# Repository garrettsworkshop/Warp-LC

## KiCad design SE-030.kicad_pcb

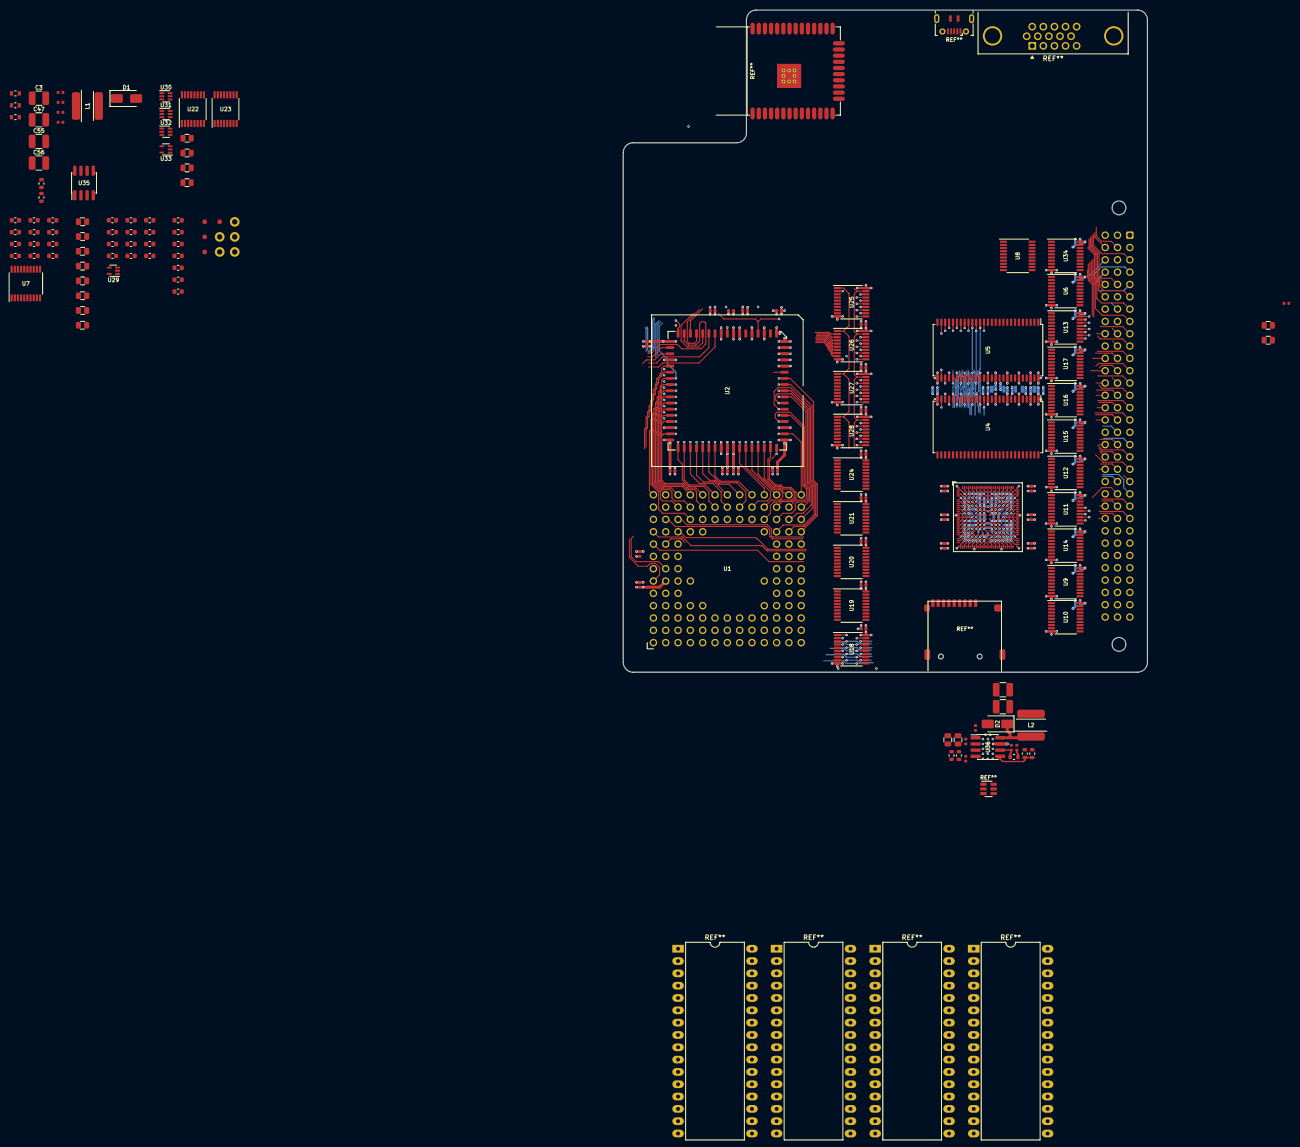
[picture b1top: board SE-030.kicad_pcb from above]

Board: 6 copper layers, 108.1 x 136.5 mm, 121 parts (1 on the bottom side), 229 nets.

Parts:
C1, C2, C54, C61: 100n; C_0402
C3, C47, C55, C56: 47u; C_1210
C4, C5, C6, C7, C8, C9, C10, C11, C12, C13, C14, C15, C57, C58, C59, C60: 10u; C_0805
C16, C17, C18, C19, C20, C21, C22, C23, C24, C25, C26, C27, C28, C29, C30, C31, C32, C33, C34, C35, C36, C37, C38, C39, C40, C41, C42, C43, C44, C45, C46: 2u2; C_0603
C48, C53: 10n; C_0402
C49, C52: 1n; C_0402
C50, C51: 47p; C_0402
D1, D2: B340LB; D_SMA
FID1, FID2, FID3, FID4: Fiducial
H1, H2, H3, H4, H5: PasteHole_1.1mm_PTH
J2: MacLCPDS; DIN41612_R_3x32_Male_Vertical_THT
L1, L2: 4u7; TaiyoYuden_NRS6028
R5, R13: 3k3; R_0603
R6: 10k; R_0603
R7, R10: 29k4; R_0603
R8, R9, R11, R12: Rl; R_0603
R14: 8k2; R_0603
U1: MC68030RC; PGA-128_MC68030
U2: MC68882FN; PLCC-68_SMDSocket
U3: LFE5U-12F-BG256; Lattice_CABGA-256_14x14mm
U4, U5: W9825G6KH-6; TSOP-II-54_22.2x10.16mm_P0.8mm
U6, U8, U9, U10, U11, U12, U34: 74AHCT573PW; TSSOP-20_4.4x6.5mm_P0.65mm
U7, U18, U19, U20, U21, U24: 74LVC244APW; TSSOP-20_4.4x6.5mm_P0.65mm
U13: 74LVC245APW; TSSOP-20_4.4x6.5mm_P0.65mm
U14, U15, U16, U17, U25, U26, U27, U28: 74AHC245APW; TSSOP-20_4.4x6.5mm_P0.65mm
U22, U23: 74LVC138APW; TSSOP-16_4.4x5mm_P0.65mm
U29: 74LVC1G125GW; SOT-353
U30: 741G3208GW; SOT-363
U31, U32: 74LVC1G332GW; SOT-363
U33: 741G08GW; SOT-353
U35, U36: TPS54331D; SOIC-8_3.9mm

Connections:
+1V1: C55.1, C56.1, L2.2, R13.1, U3.G6 (Vcc), U3.G7 (Vcc), U3.G9 (Vcc), U3.L8 (Vcc), U3.L9 (Vcc), U3.L10 (Vcc)
+2V5: U3.G11 (VccAUX), U3.L7 (VccAUX)
+3V3: C3.1, C16.1, C17.1, C18.1, C19.1, C20.1, C21.1, C22.1, C23.1, C24.1, C25.1, C26.1, C27.1, C28.1, C29.1, C30.1, C31.1, C32.1, C33.1, C34.1, C35.1, C36.1, C37.1, C38.1, C39.1, C40.1, C41.1, C42.1, C43.1, C44.1, C45.1, C46.1, C47.1, L1.2, R6.1, U3.F6 (VccIO0), U3.F7 (VccIO0), U3.F10 (VccIO1), U3.F11 (VccIO1), U3.H6 (VccIO7), U3.H7 (VccIO7), U3.H11 (VccIO2), U3.J6 (VccIO6), U3.J7 (VccIO6), U3.J11 (VccIO2), U3.K11 (VccIO3), U3.L6 (VccIO8), U3.L11 (VccIO3), U4.1, U4.3, U4.9, U4.14, U4.27, U4.43, U4.49, U5.1, U5.3, U5.9, U5.14, U5.27, U5.43, U5.49, U7.20 (Vcc), U13.20 (Vcc), U14.20 (Vcc), U15.20 (Vcc), U16.20 (Vcc), U17.20 (Vcc), U18.20 (Vcc), U19.20 (Vcc), U20.20 (Vcc), U21.20 (Vcc), U22.16 (Vcc), U23.16 (Vcc), U24.20 (Vcc), U25.20, U26.20, U27.20, U28.20, U29.5 (Vcc), U30.5 (Vcc), U31.5 (Vcc), U32.5 (Vcc), U33.5 (Vcc)
+5V: C4.1, C5.1, C12.1, C13.1, C14.1, C15.1, J2.B3 (+5V), J2.B4 (+5V), U1.A1 (~BR), U1.C3 (~BGACK), U1.C6 (Vcc), U1.D4 (Vcc), U1.D10 (Vcc), U1.F2 (Vcc), U1.F11 (Vcc), U1.F13 (~MMUDIS), U1.H1 (Vcc), U1.H3 (Vcc), U1.H12 (~CDIS), U1.K4 (Vcc), U1.K10 (Vcc), U1.L6 (Vcc), U2.10, U2.16, U2.17, U2.18, U2.26, U2.27, U2.43, U2.52, U2.53, U2.61, U6.11 (~LE), U6.20 (Vcc), U8.20 (Vcc), U9.20 (Vcc), U10.20 (Vcc), U11.20 (Vcc), U12.20 (Vcc), U34.11 (~LE), U34.20 (Vcc)
+12V: C8.1, C9.1, J2.A32 (+12V)
-5V: C6.1, C7.1, J2.C32 (-5V)
-12V: C10.1, C11.1
/CPUBuf/A13: U1.A12 (A13), U23.6 (E3)
/CPUBuf/A14: U1.B10 (A14), U23.3 (A2)
/CPUBuf/A15: U1.A11 (A15), U23.2 (A1)
/CPUBuf/A16: U1.B9 (A16), U23.1 (A0)
/CPUBuf/A17: U1.A10 (A17), U22.6 (E3)
/CPUBuf/A18: U1.C8 (A18), U23.5 (~E2)
/CPUBuf/A19: U1.A9 (A19), U22.5 (~E2)
/CPUBuf/A30: U1.A3 (A30), U31.3 (B)
/CPUBuf/A31: U1.B3 (A31), U31.1 (A)
/CPUBuf/CPU_D0: U2.3, U25.9
/CPUBuf/CPU_D1: U2.2, U25.8
/CPUBuf/CPU_D2: U2.1, U25.6
/CPUBuf/CPU_D3: U2.68, U25.4
/CPUBuf/CPU_D4: U2.67, U25.2
/CPUBuf/CPU_D5: U2.66, U25.3
/CPUBuf/CPU_D6: U2.65, U25.5
/CPUBuf/CPU_D7: U2.64, U25.7
/CPUBuf/CPU_D8: U2.62, U26.3
/CPUBuf/CPU_D9: U2.60, U26.2
/CPUBuf/CPU_D10: U2.59, U26.4
/CPUBuf/CPU_D11: U2.58, U26.5
/CPUBuf/CPU_D12: U2.57, U26.6
/CPUBuf/CPU_D13: U2.56, U26.7
/CPUBuf/CPU_D14: U2.55, U26.8
/CPUBuf/CPU_D15: U2.54, U26.9
/CPUBuf/CPU_D16: U2.50, U27.2
/CPUBuf/CPU_D17: U2.49, U27.3
/CPUBuf/CPU_D18: U2.48, U27.4
/CPUBuf/CPU_D19: U2.47, U27.5
/CPUBuf/CPU_D20: U2.46, U27.6
/CPUBuf/CPU_D21: U2.45, U27.7
/CPUBuf/CPU_D22: U2.44, U27.9
/CPUBuf/CPU_D23: U2.42, U27.8
/CPUBuf/CPU_D24: U2.40, U28.2
/CPUBuf/CPU_D25: U2.39, U28.3
/CPUBuf/CPU_D26: U2.38, U28.4
/CPUBuf/CPU_D27: U2.37, U28.5
/CPUBuf/CPU_D28: U2.36, U28.6
/CPUBuf/CPU_D29: U2.35, U28.7
/CPUBuf/CPU_D30: U2.34, U28.8
/CPUBuf/CPU_D31: U2.33, U28.9
/CPUBuf/FC0: U1.D2 (FC0), U22.1 (A0), U24.15 (2A1)
/CPUBuf/FC1: U1.C1 (FC1), U22.2 (A1), U24.17 (2A0)
/CPUBuf/FC2: U1.D1 (FC2), U22.3 (A2), U24.8 (1A3)
/CPUBuf/R~W: U1.L3 (R~W), U24.4 (1A1), U24.6 (1A2), U31.6 (C)
/CPUBuf/SIZ0: U1.L2 (SIZ0), U24.13 (2A2)
/CPUBuf/SIZ1: U1.K3 (SIZ1), U24.11 (2A3)
/CPUBuf/~AS: U1.J2 (~AS), U7.17 (2A0), U33.1 (A)
/CPUBuf/~CBREQ: U1.K1 (~CBREQ), U7.13 (2A2)
/Control/CCLK: U1.E1 (CLK), U3.N9 (CCLK), U33.2 (B)
/Control/CPU_DDIR: U25.1, U26.1, U27.1, U28.1
/Control/CPU_D~OE: U25.19, U26.19, U27.19, U28.19
/Control/IOA~OE: U6.1 (~OE), U9.1 (~OE), U10.1 (~OE), U11.1 (~OE), U12.1 (~OE), U34.1 (~OE)
/Control/IOD~OE: U14.19 (~OE), U15.19 (~OE), U16.19 (~OE), U17.19 (~OE)
/Control/RAM_~CAS: U4.17, U5.17
/Control/RAM_~CS: U4.19, U5.19
/Control/RAM_~RAS: U4.18, U5.18
/Control/RAM_~WE: U4.16, U5.16
/MC68k/~IPL0: J2.A22 (~IPL0), U1.H13 (~IPL0)
/MC68k/~IPL1: J2.C21 (~IPL1), U1.G13 (~IPL1)
/MC68k/~IPL2: J2.B21 (~IPL2), U1.G12 (~IPL2)
/MC68k/~RESET: J2.C7 (~RESET), U1.F12 (~RESET), U13.12 (B6)
/MC68k/~STERM: U1.G1 (~STERM), U30.4 (Y)
/PDS/A0: J2.C17 (A0), U6.17 (Q2), U12.19 (Q0)
/PDS/A1: J2.A18 (A1), U6.16 (Q3), U12.18 (Q1)
/PDS/A2: J2.B25 (A2), U9.18 (Q1)
/PDS/A3: J2.C25 (A3), U9.17 (Q2)
/PDS/A4: J2.A25 (A4), U9.19 (Q0)
/PDS/A5: J2.C26 (A5), U9.14 (Q5)
/PDS/A6: J2.A26 (A6), U9.16 (Q3)
/PDS/A7: J2.C27 (A7), U10.19 (Q0)
/PDS/A8: J2.B28 (A8), U10.17 (Q2)
/PDS/A9: J2.A28 (A9), U10.18 (Q1)
/PDS/A10: J2.C28 (A10), U10.16 (Q3)
/PDS/A11: J2.A27 (A11), U9.13 (Q6)
/PDS/A12: J2.B26 (A12), U9.15 (Q4)
/PDS/A13: J2.B27 (A13), U9.12 (Q7)
/PDS/A14: J2.C29 (A14), U10.13 (Q6)
/PDS/A15: J2.B29 (A15), U10.14 (Q5), U11.12 (Q7)
/PDS/A16: J2.A29 (A16), U10.15 (Q4), U11.13 (Q6)
/PDS/A17: J2.B30 (A17), U11.14 (Q5)
/PDS/A18: J2.A30 (A18), U10.12 (Q7), U11.15 (Q4)
/PDS/A19: J2.C30 (A19), U11.16 (Q3)
/PDS/A20: J2.A21 (A20), U11.17 (Q2)
/PDS/A21: J2.C20 (A21), U11.18 (Q1)
/PDS/A22: J2.B20 (A22), U11.19 (Q0)
/PDS/A23: J2.A20 (A23), U12.12 (Q7)
/PDS/A24: J2.C19 (A24), U12.13 (Q6)
/PDS/A25: J2.B19 (A25), U12.14 (Q5)
/PDS/A26: J2.A19 (A26), U12.15 (Q4)
/PDS/A27: J2.C18 (A27), U12.16 (Q3)
/PDS/A31: J2.B18 (A31), U12.17 (Q2)
/PDS/C16M: J2.B7 (C16M), U13.14 (B4)
/PDS/D0: J2.B24 (D0), U14.12 (B6)
/PDS/D1: J2.A24 (D1), U14.13 (B5)
/PDS/D2: J2.A23 (D2), U14.16 (B2)
/PDS/D3: J2.B22 (D3), U14.18 (B0)
/PDS/D4: J2.C22 (D4), U14.17 (B1)
/PDS/D5: J2.B23 (D5), U14.15 (B3)
/PDS/D6: J2.C23 (D6), U14.14 (B4)
/PDS/D7: J2.C24 (D7), U14.11 (B7)
/PDS/D8: J2.C16 (D8), U15.11 (B7)
/PDS/D9: J2.B16 (D9), U15.12 (B6)
/PDS/D10: J2.A16 (D10), U15.13 (B5)
/PDS/D11: J2.C15 (D11), U15.14 (B4)
/PDS/D12: J2.B15 (D12), U15.15 (B3)
/PDS/D13: J2.A15 (D13), U15.16 (B2)
/PDS/D14: J2.C14 (D14), U15.17 (B1)
/PDS/D15: J2.B14 (D15), U15.18 (B0)
/PDS/D16: J2.A14 (D16), U16.11 (B7)
/PDS/D17: J2.C13 (D17), U16.12 (B6)
/PDS/D18: J2.B13 (D18), U16.13 (B5)
/PDS/D19: J2.A13 (D19), U16.14 (B4)
/PDS/D20: J2.C12 (D20), U16.15 (B3)
/PDS/D21: J2.B12 (D21), U16.16 (B2)
/PDS/D22: J2.A12 (D22), U16.17 (B1)
/PDS/D23: J2.C11 (D23), U16.18 (B0)
/PDS/D24: J2.B11 (D24), U17.11 (B7)
/PDS/D25: J2.A11 (D25), U17.12 (B6)
/PDS/D26: J2.C10 (D26), U17.13 (B5)
/PDS/D27: J2.B10 (D27), U17.14 (B4)
/PDS/D28: J2.A10 (D28), U17.15 (B3)
/PDS/D29: J2.C9 (D29), U17.16 (B2)
/PDS/D30: J2.B9 (D30), U17.17 (B1)
/PDS/D31: J2.A9 (D31), U17.18 (B0)
/PDS/FC0: J2.A7 (FC0), U6.19 (Q0)
/PDS/FC1: J2.C6 (FC1), U34.12 (Q7)
/PDS/FC2: J2.A6 (FC2), U34.13 (Q6)
/PDS/R~W: J2.B2 (R~W), U34.19 (Q0)
/PDS/SIZ0: J2.C5 (SIZ0), U34.14 (Q5)
/PDS/SIZ1: J2.B5 (SIZ1), U34.15 (Q4)
/PDS/~AS: J2.A3 (~AS), U34.16 (Q3)
/PDS/~BERR: J2.C3 (~BERR), U13.19 (~OE)
/PDS/~BR: J2.B17 (~BR), U8.14 (Q5)
/PDS/~DSACK0: J2.C4 (~DSACK0), U13.17 (B1)
/PDS/~DSACK1: J2.A4 (~DSACK1), U13.18 (B0)
/PDS/~DS: J2.C2 (~DS), U34.17 (Q2)
/PDS/~HALT: J2.A5 (~HALT), U13.16 (B2)
/PDS/~RMC: J2.A8 (~RMC), U6.18 (Q1)
/PDSBuf/AD0: U8.9 (D7), U12.2 (D0)
/PDSBuf/AD1: U8.8 (D6), U12.3 (D1)
/PDSBuf/AD3: U8.6 (D4), U12.5 (D3)
/PDSBuf/AD4: U8.5 (D3), U12.6 (D4)
/PDSBuf/AD5: U8.4 (D2), U12.7 (D5)
/PDSBuf/AD6: U8.3 (D1), U12.8 (D6)
/PDSBuf/AD7: U8.2 (D0), U12.9 (D7)
/PDSBuf/AoutLE: U9.11 (~LE), U10.11 (~LE), U11.11 (~LE), U12.11 (~LE)
/PDSBuf/DDIR: U14.1 (AtoB), U15.1 (AtoB), U16.1 (AtoB), U17.1 (AtoB), U34.18 (Q1)
/PDSBuf/FSB_A25: U9.5 (D3), U9.8 (D6)
/PDSBuf/FSB_A26: U9.4 (D2), U9.7 (D5)
/PDSBuf/FSB_A27: U9.2 (D0), U9.3 (D1), U9.6 (D4)
/PDSBuf/IOR~W: U34.2 (D0), U34.3 (D1)
/PDSBuf/LFC0: U6.2 (D0), U8.16 (Q3)
/PDSBuf/LFC1: U8.17 (Q2), U34.9 (D7)
/PDSBuf/LFC2: U8.18 (Q1), U34.8 (D6)
/RAM/BA0: U4.20, U5.20
/RAM/BA1: U4.21, U5.21
/RAM/CKE: U4.37, U5.37
/RAM/D0: U4.2, U25.11
/RAM/D1: U4.4, U25.12
/RAM/D2: U4.5, U25.14
/RAM/D3: U4.7, U25.16
/RAM/D4: U4.8, U25.18
/RAM/D5: U4.10, U25.17
/RAM/D6: U4.11, U25.15
/RAM/D7: U4.13, U25.13
/RAM/D8: U4.42, U26.17
/RAM/D9: U4.44, U26.18
/RAM/D10: U4.45, U26.16
/RAM/D11: U4.47, U26.15
/RAM/D12: U4.48, U26.14
/RAM/D13: U4.50, U26.13
/RAM/D14: U4.51, U26.12
/RAM/D15: U4.53, U26.11
/RAM/D16: U5.2, U27.18
/RAM/D17: U5.4, U27.17
/RAM/D18: U5.5, U27.16
/RAM/D19: U5.7, U27.15
/RAM/D20: U5.8, U27.14
/RAM/D21: U5.10, U27.13
/RAM/D22: U5.11, U27.11
/RAM/D23: U5.13, U27.12
/RAM/D24: U5.42, U28.18
/RAM/D25: U5.44, U28.17
/RAM/D26: U5.45, U28.16
/RAM/D27: U5.47, U28.15
/RAM/D28: U5.48, U28.14
/RAM/D29: U5.50, U28.13
/RAM/D30: U5.51, U28.12
/RAM/D31: U5.53, U28.11
/RAM/RA0: U4.23, U5.23
/RAM/RA1: U4.24, U5.24
/RAM/RA2: U4.25, U5.25
/RAM/RA3: U4.26, U5.26
/RAM/RA4: U4.29, U5.29
/RAM/RA5: U4.30, U5.30
/RAM/RA6: U4.31, U5.31
/RAM/RA7: U4.32, U5.32
/RAM/RA8: U4.33, U5.33
/RAM/RA9: U4.34, U5.34
/RAM/RA10: U4.22, U5.22
/RAM/RA11: U4.35, U5.35
/RAM/RA12: U4.36, U5.36
GND: C1.2, C3.2, C4.2, C5.2, C6.2, C7.2, C8.2, C9.2, C10.2, C11.2, C12.2, C13.2, C14.2, C15.2, C16.2, C17.2, C18.2, C19.2, C20.2, C21.2, C22.2, C23.2, C24.2, C25.2, C26.2, C27.2, C28.2, C29.2, C30.2, C31.2, C32.2, C33.2, C34.2, C35.2, C36.2, C37.2, C38.2, C39.2, C40.2, C41.2, C42.2, C43.2, C44.2, C45.2, C46.2, C47.2, C48.2, C49.2, C50.2, C51.2, C52.2, C53.2, C55.2, C56.2, C57.2, C58.2, C59.2, C60.2, C61.2, D1.2 (A), D2.2 (A), H1.1, H2.1, H3.1, H4.1, H5.1, J2.B6 (GND), J2.B8 (GND), J2.B32 (GND), R5.2, R9.2, R12.2, R14.2, U1.C5 (GND), U1.C7 (GND), U1.C9 (GND), U1.E2 (~AVEC), U1.E3 (GND), U1.E11 (GND), U1.F3 (GND), U1.G3 (GND), U1.G11 (GND), U1.J3 (GND), U1.J11 (GND), U1.L5 (GND), U1.L7 (GND), U1.L8 (GND), U1.L9 (GND), U2.5, U2.6, U2.7, U2.8, U2.9, U2.12, U2.14, U2.19, U2.30, U2.41, U2.51, U2.63, U3.A1 (GND), U3.A16 (GND), U3.D2 (GND), U3.D15 (GND), U3.F8 (GND), U3.F9 (GND), U3.G8 (GND), U3.G10 (GND), U3.H1 (GND), U3.H8 (GND), U3.H9 (GND), U3.H10 (GND), U3.H16 (GND), U3.J8 (GND), U3.J9 (GND), U3.J10 (GND), U3.K6 (GND), U3.K7 (GND), U3.K8 (GND), U3.K9 (GND), U3.K10 (GND), U3.N2 (GND), U3.N15 (GND), U3.T1 (GND), U3.T5 (GND), U3.T12 (GND), U3.T16 (GND), U4.6, U4.12, U4.28, U4.41, U4.46, U4.52, U4.54, U5.6, U5.12, U5.28, U5.41, U5.46, U5.52, U5.54, U6.10 (GND), U7.1 (1~OE), U7.2 (1A0), U7.4 (1A1), U7.5 (2Y1), U7.6 (1A2), U7.8 (1A3), U7.9 (2Y3), U7.10 (GND), U7.11 (2A3), U7.12 (1Y3), U7.14 (1Y2), U7.15 (2A1), U7.16 (1Y1), U7.18 (1Y0), U7.19 (2~OE), U8.1 (~OE), U8.10 (GND), U9.10 (GND), U10.10 (GND), U11.10 (GND), U12.10 (GND), U13.1 (AtoB), U13.6 (A4), U13.8 (A6), U13.10 (GND), U13.11 (B7), U13.13 (B5), U13.15 (B3), U14.10 (GND), U15.10 (GND), U16.10 (GND), U17.10 (GND), U18.1 (1~OE), U18.10 (GND), U18.19 (2~OE), U19.1 (1~OE), U19.10 (GND), U19.19 (2~OE), U20.1 (1~OE), U20.10 (GND), U20.19 (2~OE), U21.1 (1~OE), U21.10 (GND), U21.19 (2~OE), U22.4 (~E1), U22.8 (GND), U23.4 (~E1), U23.8 (GND), U24.1 (1~OE), U24.10 (GND), U24.19 (2~OE), U25.10, U26.10, U27.10, U28.10, U29.2 (A), U29.3 (GND), U30.2 (GND), U31.2 (GND), U32.2 (GND), U33.3 (GND), U34.10 (GND), U35.7 (GND), U36.7 (GND)
unnamed: C49.1, R7.2
unnamed: C52.1, R10.2
unnamed: C2.2, D1.1 (K), L1.1, U35.8 (PH)
unnamed: C54.2, D2.1 (K), L2.1, U36.8 (PH)
unnamed: U22.7 (~Q7), U32.1 (A)
unnamed: U23.15 (~Q0), U32.3 (B)
unnamed: U30.1 (A), U31.4 (Y)
unnamed: C2.1, U35.1 (BOOT)
unnamed: C50.1, R7.1, U35.6 (COMP)
unnamed: R8.2, R9.1, U35.3 (EN)
unnamed: C48.1, U35.4 (SS)
unnamed: C1.1, C57.1, C58.1, C59.1, C60.1, C61.1, R8.1, R11.1, U35.2 (VIN), U36.2 (VIN)
unnamed: R5.1, R6.2, U35.5 (VSENSE)
unnamed: C54.1, U36.1 (BOOT)
unnamed: C51.1, R10.1, U36.6 (COMP)
unnamed: R11.2, R12.1, U36.3 (EN)
unnamed: C53.1, U36.4 (SS)
unnamed: R13.2, R14.1, U36.5 (VSENSE)

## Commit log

2021-10-29 add from other repo
2021-10-29 screwing around
2021-10-29 Clock stuff
2021-10-31 Cache stuff
2021-11-02 More cache stuff
2021-11-02 idk more
2023-05-04 lots
